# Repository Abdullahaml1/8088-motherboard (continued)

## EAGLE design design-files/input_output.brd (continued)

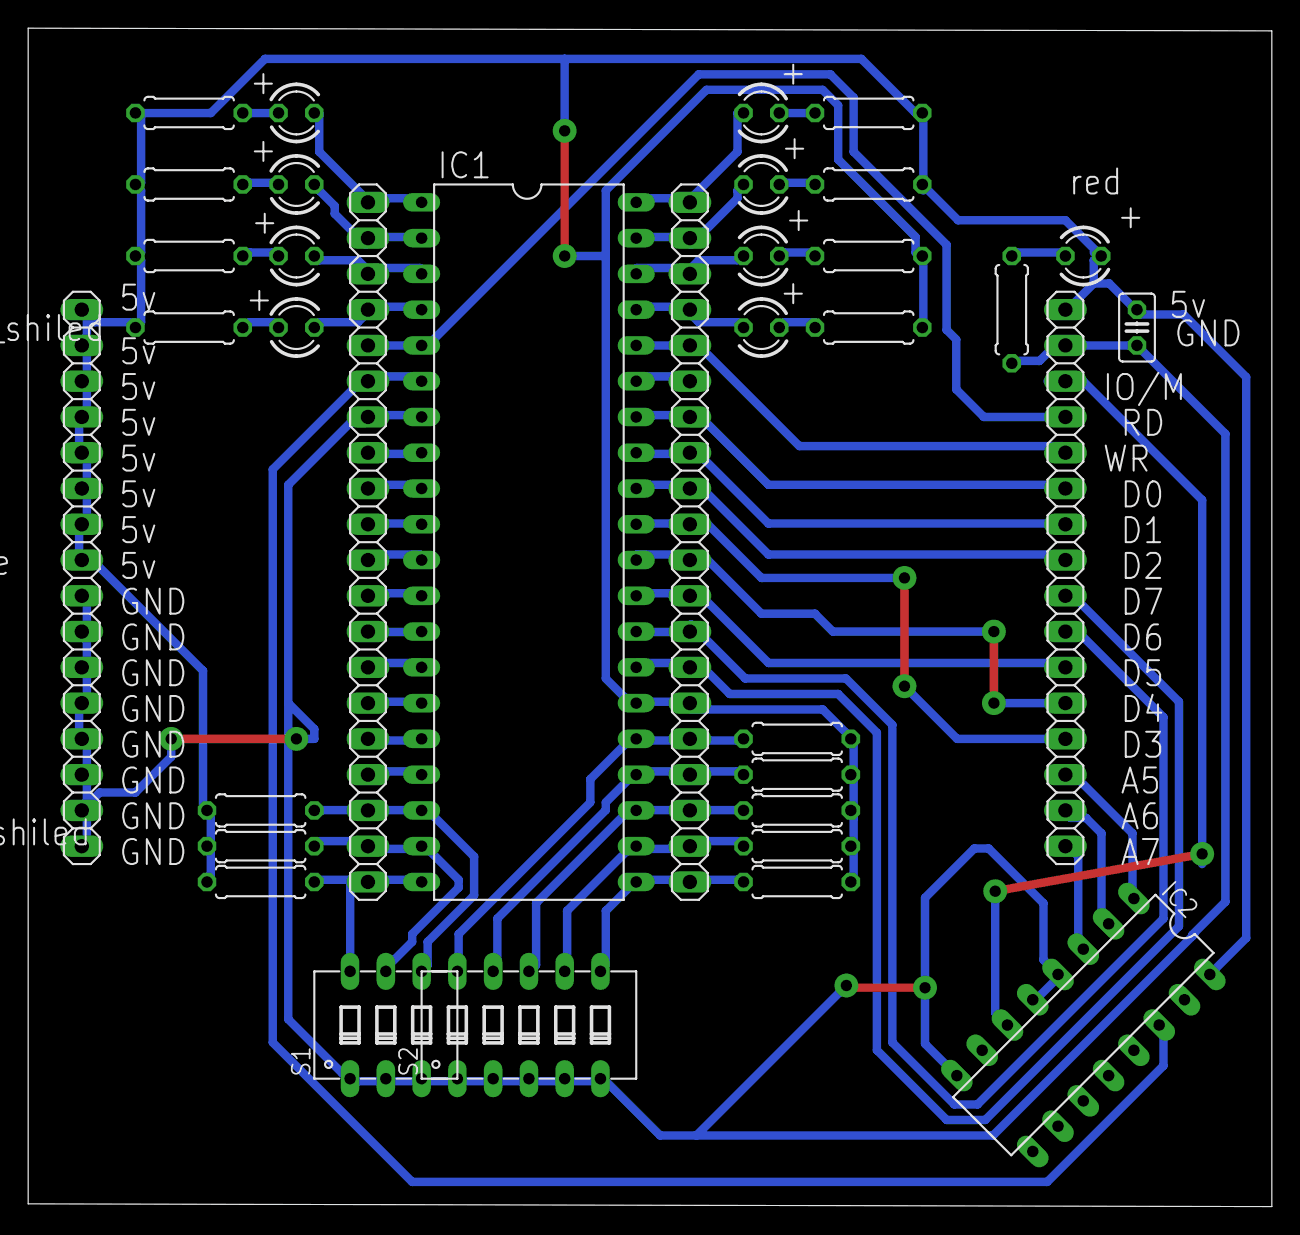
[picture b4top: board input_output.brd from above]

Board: 2 copper layers, 88.3 x 83.7 mm, 35 parts (0 on the bottom side), 53 nets.

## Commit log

2020-03-23 Adding design files and documentations.
2020-03-23 updating Readme with table of content
2020-03-23 Update the readme
2020-03-23 fixing table of content
